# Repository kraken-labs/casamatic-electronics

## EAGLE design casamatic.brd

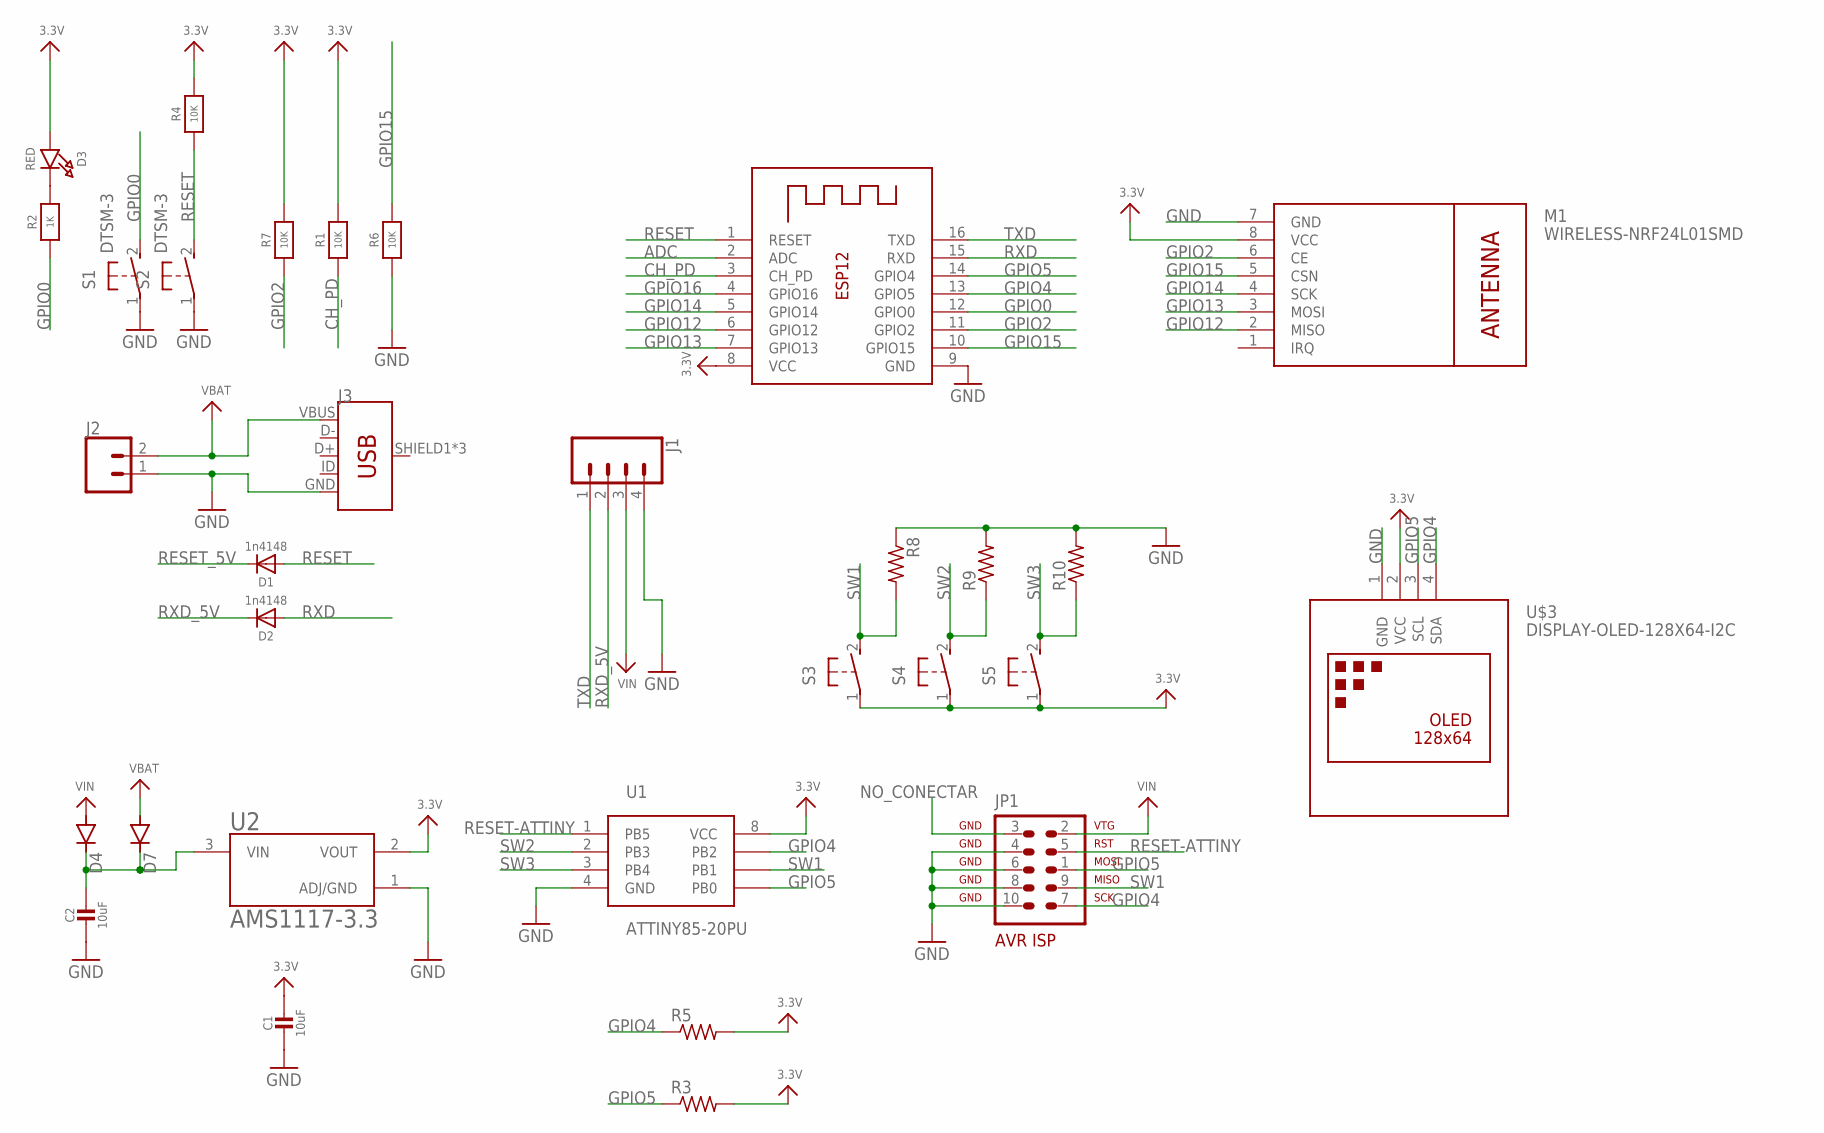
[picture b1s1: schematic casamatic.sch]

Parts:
C1, C2: 10uF; 0603-NO
D1, D2: 1n4148; SOD-323
D3: RED; CHIPLED_0805_NOOUTLINE
D4, D7: DIODE-DO214AA; DO214AA
J1: CONN_04; 1X04
J2: CONN_02; 1X02
J3: USB_MICRO-B_FEMALE-SMT; USB-B-MICRO-SMD
JP1: AVR-ISP-10
M1: WIRELESS-NRF24L01SMD; WIRELESS-NRF24L01-SMD
R1, R4, R6, R7: 10K; 0805-NO
R2: 1K; 0805-NO
R3, R5, R8, R9, R10: R-US_R0805; R0805
S1, S2, S3, S4, S5: DTSM-3
U1: ATTINY85-20PU; PDIP-8
U2: AMS1117-3.3; SOT229P700X180-4N
U$3: DISPLAY-OLED-128X64-I2C
X1: ESP-12

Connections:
3.3V: C1.1, D3.A, M1.8 (VCC), R1.2, R3.2, R4.2, R5.2, R7.2, S3.1, S4.1, S5.1, U1.8 (VCC), U2.2 (VOUT), U$3.2 (VCC), X1.8 (VCC)
ADC: X1.2 (ADC)
CH_PD: R1.1, X1.3 (CH_PD)
GND: C1.2, C2.2, J1.4, J2.1, J3.GND, JP1.4, JP1.6, JP1.8, JP1.10, M1.7 (GND), R6.1, R8.1, R9.2, R10.2, S1.1, S2.1, U1.4 (GND), U2.1 (ADJ/GND), U$3.1 (GND), X1.9 (GND)
GPIO0: R2.1, S1.2, X1.12 (GPIO0)
GPIO2: M1.6 (CE), R7.1, X1.11 (GPIO2)
GPIO4: JP1.7, R5.1, U1.7 (PB2), U$3.4 (SDA), X1.13 (GPIO5)
GPIO5: JP1.1, R3.1, U1.5 (PB0), U$3.3 (SCL), X1.14 (GPIO4)
GPIO12: M1.2 (MISO), X1.6 (GPIO12)
GPIO13: M1.3 (MOSI), X1.7 (GPIO13)
GPIO14: M1.4 (SCK), X1.5 (GPIO14)
GPIO15: M1.5 (CSN), R6.2, X1.10 (GPIO15)
GPIO16: X1.4 (GPIO16)
unnamed: D3.C, R2.2
unnamed: C2.1, D4.C, D7.C, U2.3 (VIN)
NO_CONECTAR: JP1.3
RESET: D1.A, R4.1, S2.2, X1.1 (RESET)
RESET-ATTINY: JP1.5, U1.1 (PB5)
RESET_5V: D1.C
RXD: D2.A, X1.15 (RXD)
RXD_5V: D2.C, J1.2
SW1: JP1.9, R8.2, S3.2, U1.6 (PB1)
SW2: R9.1, S4.2, U1.2 (PB3)
SW3: R10.1, S5.2, U1.3 (PB4)
TXD: J1.1, X1.16 (TXD)
VBAT: D7.A, J2.2, J3.VBUS
VIN: D4.A, J1.3, JP1.2

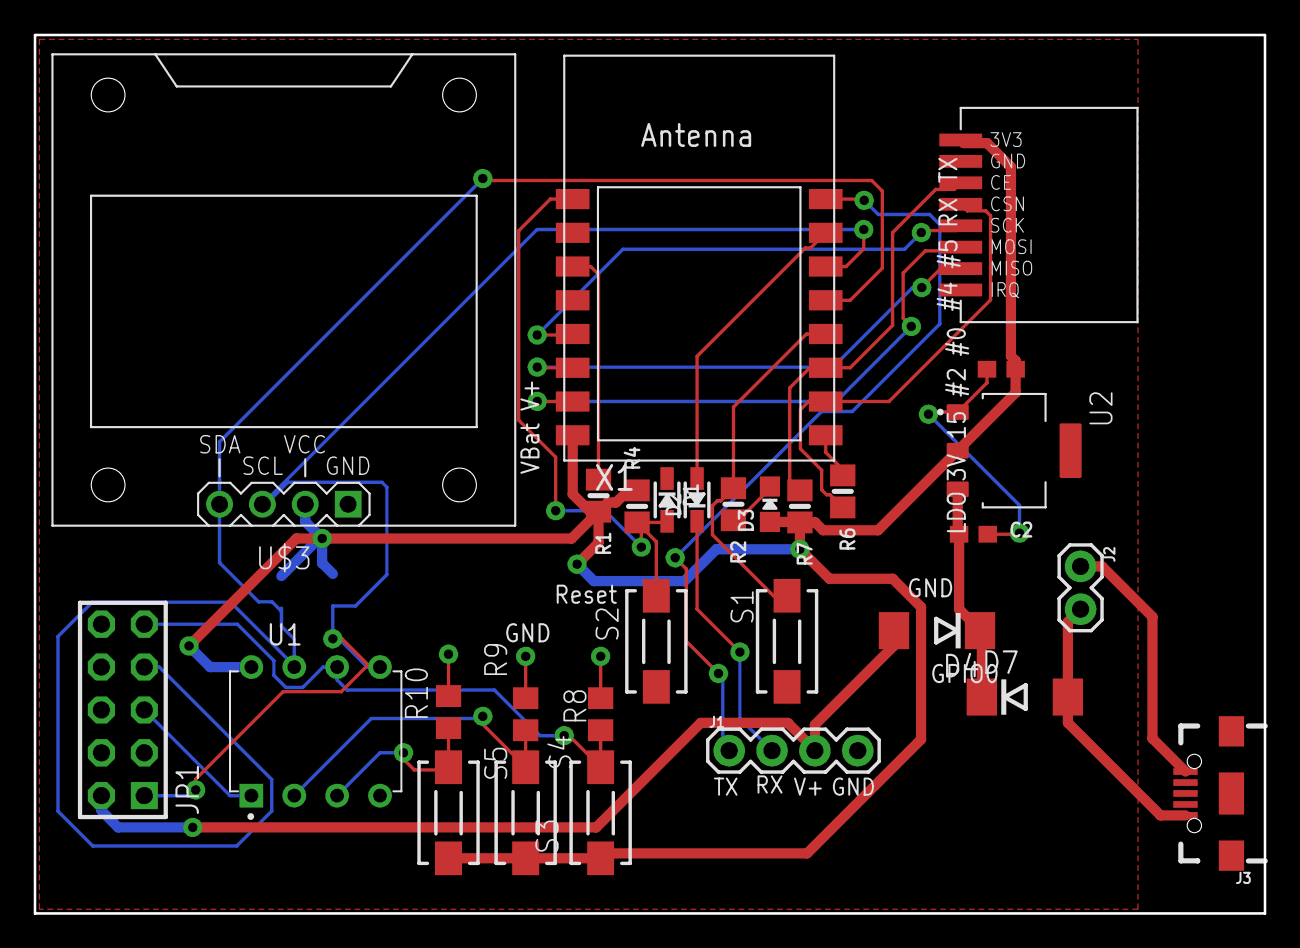
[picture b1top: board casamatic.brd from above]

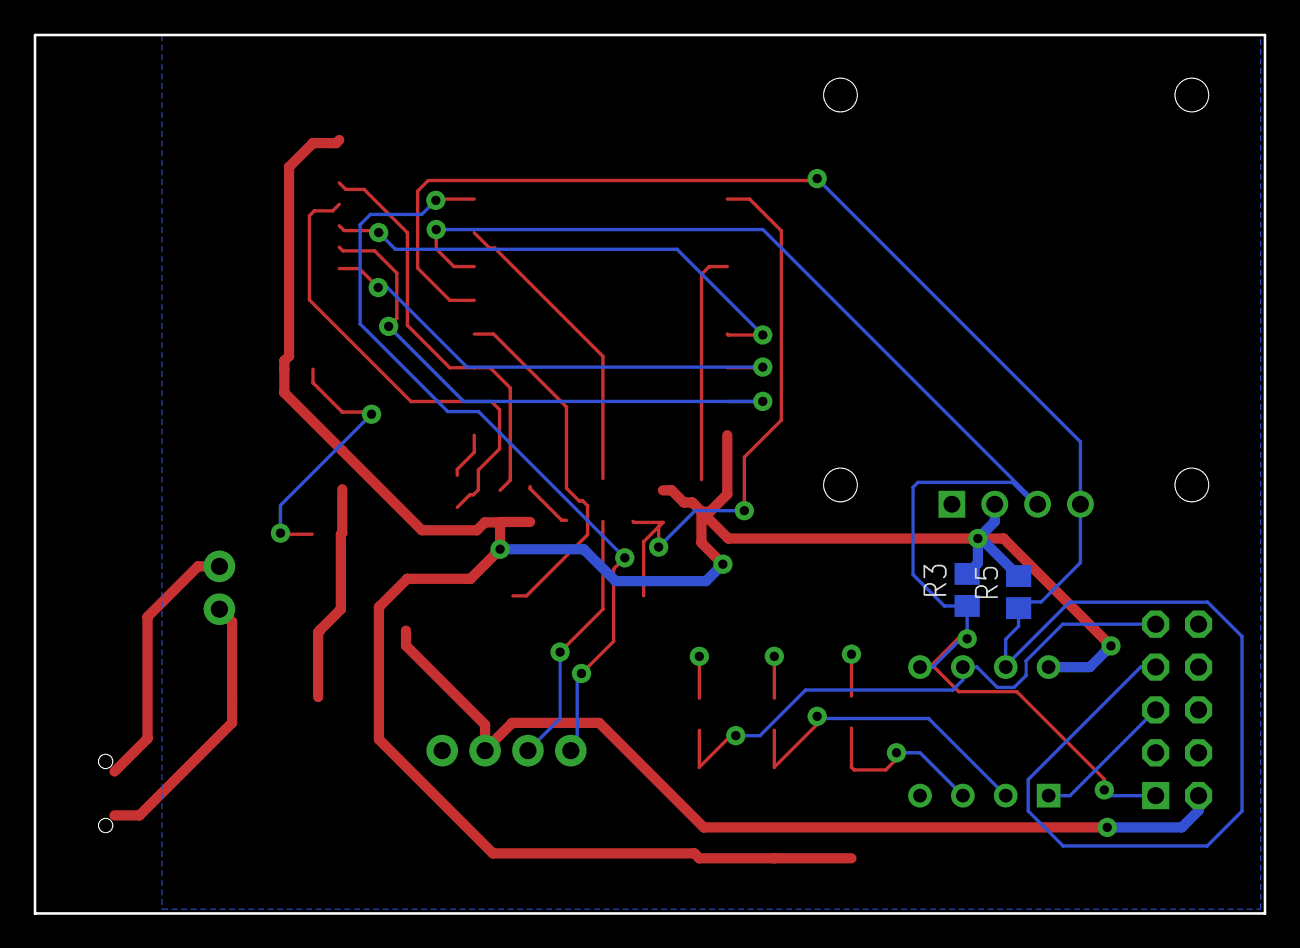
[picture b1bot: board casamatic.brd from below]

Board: 2 copper layers, 72.9 x 52.1 mm, 31 parts (2 on the bottom side), 23 nets.

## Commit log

2019-12-26 Added design rules
2019-12-26 Adjusted design rules - increased drill size by 0.05mm

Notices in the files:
parts and their libraries:
microbuilder: This work is placed in the public domain, and may be freely used for commercial and non-commercial work with the following conditions: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
diy-modules: Released under the Creative Commons Attribution 4.0 International License: http://creativecommons.org/licenses/by/4.0
